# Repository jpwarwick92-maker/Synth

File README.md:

# Synth

Firmware for a DIY 8-voice subtractive poly synth, and a browser prototype that runs
that same firmware with an on-screen control panel, so the sound engine, the display
and the panel layout can be played before any hardware exists.

## What is here

| Path | What it is |
|---|---|
| `firmware/` | The firmware core in portable C++: sound engine, oscillator engines, arpeggiator, vocoder, effects, MIDI handling, the parameter table, control logic, patches and panel take-over, soft-control modes and display drawing. No heap, no standard library, nothing platform-specific. |
| `targets/web/` | Thin wrapper that builds the core as a WebAssembly module for the browser. |
| `targets/teensy/` | Thin wrapper that builds the core for the Teensy 4.1 (PlatformIO). Compile-checked on every push; not yet run on a board. |
| `web/` | The page. It is fake hardware only: it draws the panel, reports raw control positions and MIDI bytes, shows the firmware's display buffer, lights each control's label in the colour the firmware asks for, and plays its audio. It can also plug a microphone into the firmware's audio input, send it MIDI clock, and pass on what leaves by its MIDI out. |
| `layouts/a3.json` | The panel layout in millimetres. The page draws whatever this file says. |
| `tests/native/` | Engine and display tests that render audio and display frames with no browser. `make test` leaves the frames, and a few of the renders as sound files, in `build/out`. |
| `tests/page/` | Page tests in a headless browser (mouse, touch, MIDI). |
| `docs/controls.md` | Every control with its MIDI controller number, generated from the firmware's table. |
| `hardware/` | KiCad 10 projects for the circuit boards (clock hub main board, one-LED tile) and the shared `Synth` parts library. See `hardware/README.md`. |

## The rule that keeps the code portable

Everything the real synth will run lives in `firmware/` and is built three ways from
the same files: natively for the tests, as WebAssembly for the page, and for the Teensy.
The page never decides what a control does. It reports "pot 10 is at 2731" or "button 36
went down", exactly as panel hardware would, and shows the pixels the firmware draws. An
on-screen knob never moves by itself, because a real one cannot.

Rules for code in `firmware/`:

- no memory allocation, at start-up or while playing;
- audio in blocks of at most 128 samples. Safe at any sample rate; made for 44.1 kHz
  (the Teensy) and 48 kHz (the page asks the browser for it). Above 48 kHz the longest
  delay is shorter than its setting says and the reverb's lines are scaled down;
- only `<stdint.h>` and `<stddef.h>`; maths comes from `fw_math.h`;
- the display is drawn with pixels, lines, fills and a bitmap font only, in a fixed
  set of colours named by what they are for (the frame is 4 bits per pixel), and no
  text smaller than 2 mm tall on the real display (font scale 2);
- large tables and delay lines are 16-bit where that is inaudible, to fit the
  Teensy's 1 MB of RAM. They stay in RAM: reading them from flash in the audio loop
  is too slow.

## Build and run

Needs `make`, `g++`, `clang++` with the WebAssembly linker (`lld`), Node 22 and Python 3.

```sh
make test        # engine and display tests
make site        # build the page into build/site
make serve       # serve it on http://localhost:8080
make sanitize    # the same tests with the compiler's memory checker on (slower)
make page-test   # a long run of the browser build, then the page tests
                 # (needs Playwright: cd tests/page && npm install && npx playwright install chromium)
make docs        # regenerate docs/controls.md
```

Open the page in Chrome, plug in a MIDI keyboard, press Start and allow MIDI.
The page must be served from `localhost` or over HTTPS; browsers do not allow MIDI
or the audio engine on a plain file.

Teensy compile check: `pip install platformio && pio run -d targets/teensy`.

## Using the page

- Knobs, selectors and encoders: press and circle the pointer round the control and it
  turns with you. The **Knobs** button switches to dragging up and down instead.
- Scrolling over any control also moves it (two fingers on a trackpad, or a mouse wheel).
- Hold Shift for fine movement.
- Selectors: you can also tap a stop's label. Encoders: double-tap to push.
- Faders follow the pointer along their slot.
- **Zoom display** shows the display enlarged with every pixel visible. On the panel it
  is drawn at its true physical size, which on most screens is fewer pixels than the real
  320x240 display has.
- **1:1 size** shows the panel at true physical size. It asks once for calibration
  against a bank card held to the screen.
- Each control's label stands in for a back-lit label on the real panel. It is plain
  warm white normally, and glows red to amber or blue when the control is off a loaded
  patch (see Patches below).
- **Rough pots** (among the test aids) feeds the firmware pot readings as real hardware
  gives them: a few counts of jitter and a trace of the neighbouring pot. The firmware
  smooths them, so nothing should look or sound different with it on.
- Below the panel are test aids that are not part of the synth: stand-in pitch-bend
  and mod wheels, a Test note button that holds a chord, a sustain-pedal switch and Panic.
  They behave as a keyboard set to the channel the synth plays, and Panic is sent on
  every channel.
- **Mic in** plugs this computer's microphone into the synth's audio input (use
  headphones, or the speakers feed back). The dot beside it is the light by the input
  jack. **Test clock** sends MIDI clock into the synth's MIDI in at the tempo in the box
  beside it, as a DAW or a clock hub would; pressing it again sends stop.
- **MIDI out** in the top bar picks the device the synth's MIDI out jack is plugged
  into. A MIDI keyboard, or a DAW sending notes and clock, arrives at the synth's MIDI in.

## What the prototype covers

The whole panel (layout A3) driving the voice: two oscillators plus sub and noise,
mixer, multimode filter (12 or 24 dB) with drive, filter and amp envelopes, one LFO,
glide, and poly, mono and unison modes. The display shows a home screen with a live
scope and a visual for each control as it moves.

**Panel features added while prototyping.**

- **Drift** makes each voice slightly and slowly out of tune with the others, in pitch
  and filter cutoff, as the voices of an analog poly are. At zero every voice is exact.
- **Spread** fans the voices out between the two speakers.
- **Supersaw** is the fifth stop on each Wave selector: seven saws, with Macro setting
  how far apart they are tuned.
- **DRAW** is the sixth stop on each Wave selector: a wave you draw yourself (see
  "The drawn wave" below). The Wave selectors and LFO Shape show a small picture of each
  wave instead of its name, with a doodle line for DRAW and a stepped line for random.
- **Sync** restarts oscillator 2 with every cycle of oscillator 1. With Sync on, the
  Mod page's Env>Pitch moves oscillator 2 only, which gives the classic sync sweep.
- **X-Mod** lets oscillator 2 bend oscillator 1's phase, even with oscillator 2's
  fader down.
- **Arp** has its own section: Mode, Octaves, Tempo, Gate, Hold and Chord.
- **LFO Sync** is a three-stop selector in the LFO section. FREE: one LFO that takes no
  notice of the keys. KEY: it starts again when a note begins from silence. VOICE:
  every voice has its own LFO, each a little out of step and a little off the others'
  pace, so a held chord shimmers instead of moving as one.
- **Chorus** is a knob in the Voice section, with a Type switch beside it. CHORUS is two
  slowly swept copies, one per side. ENSEMBLE is three, a third of a cycle apart, swept
  by a slow and a fast wave at once: a swirl with no one wobble to be heard in it.
- **Sub pitch** is a selector beside the Sub fader: two octaves below oscillator 1, one
  below, a fifth above, or an octave above. Sub detune (up to 25 cents either way) is
  on the Engine page.
- **Chord** remembers the shape of a chord. Hold a chord and press Chord; after that
  each single key plays that chord, moved to the key. With the arp running, one key
  arpeggiates it. Press Chord again to forget it.
- **Ladder filter** is a third setting of the filter slope on the Engine page
  (12 dB, 24 dB, Ladder): four stages with feedback round all of them, low-pass only,
  losing some bass as resonance rises. The Type selector does nothing while it is chosen.

The layout keeps knob, selector and encoder centres at least 22 mm apart and fader
centres at least 17 mm apart, and the page tests fail if any label overlaps another
label, a control, or its section's outline. The sections sit on a grid: two rows of
equal height on five shared columns, with the same gap between every pair of
neighbours. The panel is 530 x 152 mm.

**The display.** Every control has a picture that follows it: turn a control and its
picture changes, or says in words why there is nothing to show (a delay with its mix
at zero, an oscillator playing a flat drawing). The tests enforce this for every panel control and
every value on the encoder pages, from the default settings, with further tests for
the settings under which a control does nothing. On an encoder page the picture takes
the place of the scope for a moment after an encoder is turned.

The display has two sets of colours, chosen on the Setup page. **Amber** is ambers and
orange on black, for a bare display. **White** is warm whites told apart by brightness,
for a display behind amber acrylic, which turns white into amber by itself. The page's
**Amber acrylic** button lays that sheet over the on-screen display so the white set can
be judged as it will look.

**Oscillator engines.** Each oscillator has an Engine button that steps through four
engines. The Wave selector and the timbre controls mean something different under each:

| Engine | Wave selector | Macro | Color |
|---|---|---|---|
| VA | saw, square, triangle, sine, supersaw, DRAW | shapes the wave (below) | none |
| FM | ratio 1:1, 2:1, 3:1, 3.5:1, 4:1, 0.5:1 | FM amount | feedback |
| Wavetable | table 1 to 5, and table 6: the drawing | position in the table | none |
| Pluck | exciter: noise, soft, snap, string, pick, the drawing | damping | decay |

Oscillator 1's Macro is the panel knob. Its Color, and oscillator 2's Macro and Color,
are on page 2 of the Engine mode.

**Macro shapes the wave** under the VA engine, whichever wave is selected. At zero each
wave is exactly what it was before Macro shaped it (tested bit for bit), and costs no more.

| Wave | Macro (display name) | What it does |
|---|---|---|
| Saw | SOFTEN | Rounds the corners, like the slower reset of an analogue oscillator: a filter that follows the note, from 256 times its pitch down to 1.5 times. |
| Square | PULSE WIDTH | As before. |
| Triangle | SHARK FIN | Bends the ramps into capacitor curves, from a triangle to a full shark fin (a filter that follows the note, from 0 to 1 times its pitch). |
| Sine | SQUARE UP | Adds a square's odd harmonics (3rd to 15th), more of them as Macro rises: a pure sine at zero, close to a square at full. |
| Supersaw | SPREAD | How far apart the seven saws are tuned, as before. |
| DRAW | SOFTEN | Rounds the drawing's corners, as on the saw. |

Each shape is held to the loudness of its Macro-zero wave as Macro turns, and each
keeps high notes clean (nothing louder than -60 dB between the harmonics). On a
patch, Macro now matters wherever it rests on a saw, triangle or sine.

**The drawn wave.** Each patch has a drawing: 16 points joined by straight lines, one
cycle of a wave, shared by both oscillators. A new patch starts with a saw. It is
drawn on the third Engine page:

| Encoder | Turn | Push |
|---|---|---|
| 1 | moves along the 16 points | paint mode on or off: moving along then copies the height onto each point passed |
| 2 | raises or lowers the point | puts the point on the centre line |
| 3 | chooses a starting shape: saw, square, triangle, sine, flat | replaces the drawing with it |
| 4 | | smooths the drawing a little |

The page shows the drawing with the point being edited picked out, and says so when
neither oscillator is playing it. Notes that are sounding follow the drawing as it
changes, a moment behind, with a 20 ms crossfade so nothing clicks. The drawing is
turned into band-limited tables (one per octave) so it stays clean on high notes;
that takes longer than an audio block, so it is done in spare time between other work
(`fw::work()`, called by the Teensy's main loop and by the page between audio blocks).
A drawing is played at about a saw's loudness, whatever its shape; a flat one is
silent. Under the pluck engine the string is struck with the drawing's shape, at the
other exciters' loudness. The drawing is never an FM modulator (its partials would
spread far above the note and fold back), so under FM the sixth stop is a 0.5:1 ratio.

**Soft-control modes.** A mode button puts four values on the encoders. Pressing the
lit button steps to the mode's next page if it has one, then returns home. Pushing an
encoder restores its default.

| Button | Page | Encoders |
|---|---|---|
| FX 1 | Delay | time, tone, feedback, mix |
| FX 2 | 1: Compressor + reverb | compressor, reverb size, reverb tone, reverb mix |
| FX 2 | 2: Vocoder | amount, formant, consonants, smooth |
| Mod | Mod | LFO fade-in, velocity to cutoff, filter envelope to pitch, duck |
| Engine | 1: Voice | unison detune, sub detune, bend range, filter slope (12 dB, 24 dB, ladder) |
| Engine | 2: Osc engines | osc 1 Color, (empty), osc 2 Macro, osc 2 Color |
| Engine | 3: Draw | the patch's drawing (see "The drawn wave") |
| Patch | 1: Patch | slot (push to load), save here (push), guide lights, manual (push) |
| Patch | 2: Name | cursor, (empty), letter, (empty) |
| Patch | 3: Setup | display colours (amber, or white for behind amber acrylic); label lights (steady or dance) |
| Patch | 4: MIDI | clock (internal, MIDI jack, USB), channel (all, 1 to 16), thru, clock out |
| Patch | 5: Input | source (line, mic), gain (0 to 60 dB), send to (off, mix, effects), (empty) |

**Settings.** The MIDI and Input pages hold settings about the instrument, not the
sound: they are kept over a restart and a patch never changes them.

**Clock.** With Clock on INT the arp and the duck run at the Tempo knob's setting. On
MIDI or USB they follow the MIDI clock arriving at that input, and the Tempo knob is not
used (its picture says so, and shows the clock's tempo).

- The arp's sixteenth notes fall on the clock's grid. The tempo is the average spacing
  of the last beat's ticks, and the arp steps on a position that runs on smoothly at that
  tempo and is nudged towards each tick, so ticks that arrive a few milliseconds early
  or late (as they do from a computer) still give even steps.
- **Start** begins the pattern again on the next tick, and nothing plays until that
  tick. **Stop** holds the arp silent until start or continue; notes latched by Hold
  stay latched. **Continue** carries on from where it stopped, in the beat and in the
  pattern. A **song position** message moves the beat to the sender's playhead.
- After a stop, if the clock itself has gone as well (a DAW usually stops sending it), a
  fresh chord is not kept waiting: it plays from the Tempo knob. What was latched before
  the stop stays silent.
- A key pressed up to a quarter of a step late still gets that step; later than that it
  waits for the next one.
- If no clock is arriving (none yet, or it has stopped coming for half a second) the
  Tempo knob is used meanwhile, so the synth is never silent for want of a cable.
- Clock at the input that is not selected is ignored.

**MIDI in and out.** There are two connections, the MIDI jacks and USB. Notes and
controllers are played from either, on the Channel set (or on every channel).
Changing Channel lets go of every note and the pedal, since their note-offs may now
arrive on a channel that is no longer listened to.
With **Thru** on, every note and controller message that arrives is passed on, whatever
its channel: both inputs to the MIDI out jack, and the MIDI jack's input to USB (never
USB back to USB). With **Clock Out** on, the clock the synth is running on is sent too:
its own, 24 ticks to a beat at the Tempo knob's setting, when it keeps time itself; the
incoming clock with its start, stop and continue when it is following. System-exclusive
messages are not passed on. If Thru is switched off while notes are held, or a message
could not be passed on because nothing was reading the output, "all notes off" is sent
on every channel, so nothing further down the chain is left sounding. The synth's own
clock is made in the audio blocks, so on the Teensy each tick can leave up to 2.9 ms
late; the tempo it carries is exact. On the page, a device that is both a MIDI input
and the one picked for MIDI out is not listened to while it is the output: the synth
would be handed its own messages back, round and round. Use one bus each way.

**Audio input.** The firmware takes a stereo input beside its output. **Send To**
chooses where it goes: nowhere, straight to the output beside the synth's own sound
(Mix), or into the effects with it (FX). The Volume knob turns it up and down with the
synth: at the knob's usual setting the input passes at its own level. A line input is
stereo; a microphone is one channel and comes out on both sides. **Gain** is what the firmware asks of the preamp in
front of the converter, so on real hardware it is analog gain. The Input page shows the
level against the converter's limit, and the light by the jack is dark with no signal,
amber with one, and red for nearly half a second whenever the input reaches the limit.
With Send To off the output is exactly what it would be with nothing connected. The
vocoder listens to this input whatever Send To is set to.

**Vocoder** (FX 2, second page). The synth's sound, shaped by a voice at the audio
input: play notes, speak into the microphone, and the notes take on the words. The voice
is split into 16 bands from 140 Hz to 7 kHz and the level of each is followed; the
synth's sound is split into the same bands and each is turned up and down by the voice's.
It sits between the voices and the effects, on one channel (the chorus and reverb after
it can widen it again), and its four values are stored in patches.

- **Vocoder** is the amount: how much of the synth's own sound is replaced by the
  vocoded sound. At 0 it is out of the path altogether. At 100% nothing is heard unless
  a voice is arriving.
- **Formant** moves the voice's shape up or down the synth's sound, up to an octave
  either way: up sounds smaller and brighter, down larger and darker.
- **Consonants** adds hiss to the synth's top three bands, so S, T, F and SH are heard
  even on a dull sound. It is added only for breath sounds (a voice whose strength is
  nearly all at the top), and only while a note is held.
- **Smooth** sets how fast each band's level falls when the voice does, from 8 ms
  (crisp, every syllable distinct) to about a third of a second (slurred).
- With the vocoder on, its page shows the sixteen bands moving with the voice, and says
  why if nothing can be heard: no signal at the input, or no note held.
- It works best on a bright, steady sound: saw or supersaw, filter well open, sustain up.
  Set the input's Gain so the light by the jack is amber, never red. Leave Send To off
  unless the plain voice should be heard as well.

**Patches.** Sixteen slots. Every main control is a real pot, fader or switch, so
loading a patch cannot move it. Instead:

- **Saving** stores every value except master volume and Hold, and the drawing.
  Patches saved by builds before the drawing (patch version 1 or 2) are not loaded:
  their slots read as empty. An empty slot saves on
  one push of encoder 2; a used slot asks for a second push within three seconds.
- **Loading** (push encoder 1, or send a MIDI program change) sets the sound from the
  stored values. Any control that is somewhere else is then *following*: the sound uses
  the stored value, and the control is ignored until it takes over.
- **Take-over.** A pot or fader takes over when it is moved through the stored value, or
  lands within 2.5% of its travel of it (1% for Detune), so the sound never jumps.
  Touching one that has not got there shows a picture of where the panel and the patch
  are and which way to go. A selector or switch takes over on any change.
- **Guide lights.** After a load, the label of each control that is off the patch
  glows, steadily. A control that has to come up is deep red when it is a long way
  below the patch and warms to amber as it closes in; one that has to come down is deep
  cold blue far off and pales as it nears. At the patch's value the label goes back to
  plain warm white, so when no label is coloured the panel matches the patch. A
  selector's light stays on until it is on the patch's stop, even though it is already
  live. Encoder 3 switches the lights between On, Tint (a dim amber on anything still
  following) and Off.
- **Manual** (push encoder 4) drops the patch: every control goes live where it stands.
- The home screen shows the slot and name, with `*` once the sound has changed.
- A MIDI controller message for a panel parameter is treated like a one-control load:
  the control follows the incoming value until it is moved through it (or, for a
  selector, changed). That goes for master volume too.

**Dance** (Setup page, encoder 3) makes the label lights move with the sound instead of
staying plain. Each section's labels follow what that section is doing: the LFO's rise
and fall with it; the envelope faders light in turn as a note passes through Attack,
Decay, Sustain and Release; Cutoff follows the filter envelope's sweep; a ripple runs
from the oscillators through the mixer to the filter on every note; the arp's flash on
each step; Volume follows the level. Everything stays between a dim amber and a bright
cream. While a loaded patch has controls to bring back, the dance stops and the guide
lights show. On hardware this mode changes the LEDs' current many times a second, so
their supply has to be kept well away from the audio's.

On the Teensy the slots sit in the on-board EEPROM for now, which is why there are
sixteen; a memory card or the board's flash would hold far more.

**Arpeggiator and Hold.** The arp plays the held notes as sixteenth notes: up, down,
up-down, random or as played, over 1 to 4 octaves, at 40 to 240 BPM. **Hold** keeps
notes sounding after the keys are let go; the next chord replaces them. It works with
the arp on or off. While the arp runs, the sustain pedal acts as a temporary Hold.
Neither Hold nor Chord comes back on by itself after a restart.

**The LFO's MACRO destination** (it was PW) moves whatever Macro does on that oscillator:
pulse width on a square, the saw's softness, the shark fin, the sine's squaring, the
supersaw's spread, the drawing's softness, FM amount, wavetable position, pluck damping.
With Macro at zero only the upper half of the sweep acts.

**When the processor is short of time.** A target that can time its audio (the Teensy)
reports how much of each block's time was used. If that stays above about 85% the
engine drops voices one at a time, down to two at the fewest, and gives them back
after a calm spell, instead of falling behind. Saving the state (the control
positions and settings, a second after the last change) waits for silence, for up to
half a minute, because on real hardware a save can interrupt the sound. The page's
storage costs the sound nothing, so there it does not wait. Saving a patch is written
at once on either: it is asked for by hand, and must not be lost.

**Compressor** (FX 2 page) turns the loud parts down and everything back up, so one
note and a full chord come out nearer the same level and soft notes and tails are
lifted. Its one control lowers the threshold, raises the ratio (to 4:1) and adds
make-up gain together. At zero it is out of the path altogether.

**Duck** (Mod page) dips the level just after every beat and lets it come back before
the next, as a compressor keyed from a kick drum does. The beat is the arp's Tempo, or
the MIDI clock's when one is being followed (the dips then fall on that clock's beats).
On the synth's own clock, while the arp runs the beat is counted from its steps, four to
a beat, so the two cannot slip apart; otherwise (the arp off, or no key held) it runs on
by itself, starting again with any note played from silence. The first
hundredth of a second of each beat is let through, so a note played on the beat keeps
its attack.

The order is vocoder, chorus, delay, reverb, compressor, duck, then the output
limiter.

**Output** is stereo once Spread, the chorus or the reverb is in use. With Spread at
zero and every effect off, both channels carry exactly the same signal.

Not built yet: sending the input through the voices' filter, loading patches
from files, and the iPad version (Safari on iPad has no Web MIDI, so it needs a small
wrapper app).

## Publishing

`.github/workflows/build.yml` runs the tests and the Teensy compile on every push, and
publishes `build/site` to GitHub Pages on pushes to `main`. Pages must be switched on
once in the repository settings, with **GitHub Actions** as the source.

Third-party material is listed in `THIRD_PARTY.md`.

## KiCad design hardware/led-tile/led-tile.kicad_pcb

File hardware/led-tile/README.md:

# LED tile, rev A

One reverse-mount SK6812 MINI-E on a 12 × 10 mm board, used to backlight one panel
label. The clock hub uses 12 of them and the synth about 43. Tiles are chained by three
hand-soldered wires each (+5 V, data, GND), from each tile's OUT pads to the next
tile's IN pads.

| Front (faces the panel) | Back (parts and wire pads) |
|---|---|
|  |  |

Schematic: [images/schematic.svg](images/schematic.svg)

## What's on it

| Ref | Part | Why |
|---|---|---|
| D1 | SK6812MINI-E (OPSCO), KiCad footprint `LED_SK6812MINI-E_3.2x2.8mm_P1.5mm_ReverseMount` | The light. Reverse-mount: it sits on the back and shines through a hole in the board. |
| C1 | 100 nF, 0603, X7R, 16 V or more | Local supply for D1's driver chip. The datasheet calls the capacitor "essential". |
| R1 | 330 Ω, 0603 | In series with DIN. The datasheet asks for series resistors on the data pins, against static and surges. That matters here because every tile is hand-wired. |
| J1 | `Synth:WirePads_1x03_P2.80mm` | IN wire pads: GND, data, +5 V. Not a part; left out of the BOM. |
| J2 | same | OUT wire pads: GND, data, +5 V. |

## Board

- **Size:** 12 × 10 mm, 2 layers, **0.8 mm thick** (see the stack-height question below).
- **Orientation key:** one corner is cut at 45°, on the IN/GND corner. A matching pocket in the locating layer means a tile can only go in one way round, so IN and OUT can't be swapped.
- **Back:** every part and every pad. Tracks are 0.25 mm for data and 0.4 mm for power.
- **Front:** a solid ground plane under solder mask, no parts and no silkscreen. It lies flat against the spacer, and nothing printed on it can show through the lit label.
- **Ground:** reaches the plane through three vias, which are covered with mask on both sides.
- **Rules:** copper stays 0.3 mm from every board edge. The one exception is D1's pads to D1's own light hole, which sit at 0.25 mm in KiCad's footprint. `led-tile.kicad_dru` holds that exception. Check it against the chosen maker's limit before ordering.

## Things worth knowing

- **Pin numbers don't match the datasheet.** KiCad's symbol numbers D1 as 1 GND, 2 DIN, 3 VDD, 4 DOUT. The OPSCO datasheet (rev 02) calls the same pins 1 VDD, 2 DOUT, 3 GND, 4 DIN. KiCad's symbol and footprint agree with each other and with the real part: the footprint was checked pad by pad against the datasheet drawing, seen from the back. Go by the pin names. If the board maker's placement preview shows D1 turned, check it by the package's cut corner, which is the GND corner, not by "pin 1".
- **Seen from the back, IN is on the right.** The back silkscreen is printed to read correctly from the back.
- **Data level.** DIN needs at least 0.7 × VDD, which is 3.5 V at 5 V. The first tile must be fed from the main board's 5 V buffer, never straight from the Teensy's 3.3 V pin. Each tile's DOUT then drives the next tile at 5 V.
- **Current.** Each LED draws up to 12 mA per colour, 36 mA at full white, so 12 tiles can draw 0.43 A. Brightness is capped in firmware.
- **Moisture.** The LED is moisture-sensitive (MSL 5a: 24 hours out of its bag), and its peak reflow temperature is 240 °C. That matters only if the LEDs are ever hand-soldered from a bag kept at home.

## Open question: stack height

The tile is about 1.9–2.0 mm deep, from its front face to the back of the LED. The back
of D1 sticks out about 1 mm behind the 0.8 mm board, and C1 about 0.8 mm. The hub
spec's locating layer is about 1.6 mm, so the tile doesn't fit as specced. Options:

1. **A 2.0 mm or thicker locating layer.** The panel stack grows by 0.4 mm or more, so the 17 mm shaft rule grows too.
2. **Clearance holes in the steel sub-panel** under each tile's LED and C1. The steel is laser-cut anyway, so the holes cost nothing, and the stack height stays the same. The PET insulator still covers them.
3. **A thinner board** (0.6 mm). This saves only 0.2 mm, and the datasheet warns about bending stress on boards under 0.5 mm.

To settle at the feel-and-fit mock-up (hub test H2).

## Still to do before ordering

- [ ] Settle the stack-height question above.
- [ ] Panelise: a sheet of 12 tiles with snap-apart tabs and the maker's rails and fiducials (a KiCad plugin such as KiKit does this). Keep the LED's pads at right angles to the snap lines, so snapping doesn't bend the joints.
- [ ] Pick the maker. Confirm that it assembles the LED on the back, in its reversed position, and accepts the 0.25 mm pad-to-hole gap. Choose white solder mask if offered, so light reflects up into the pocket.
- [ ] Choose exact R1 and C1 part numbers from the maker's stock.
- [ ] Print the board 1:1 on paper and lay a real LED on the footprint (hub test H4).
- [ ] Independent review of the schematic and board (hub test R4).

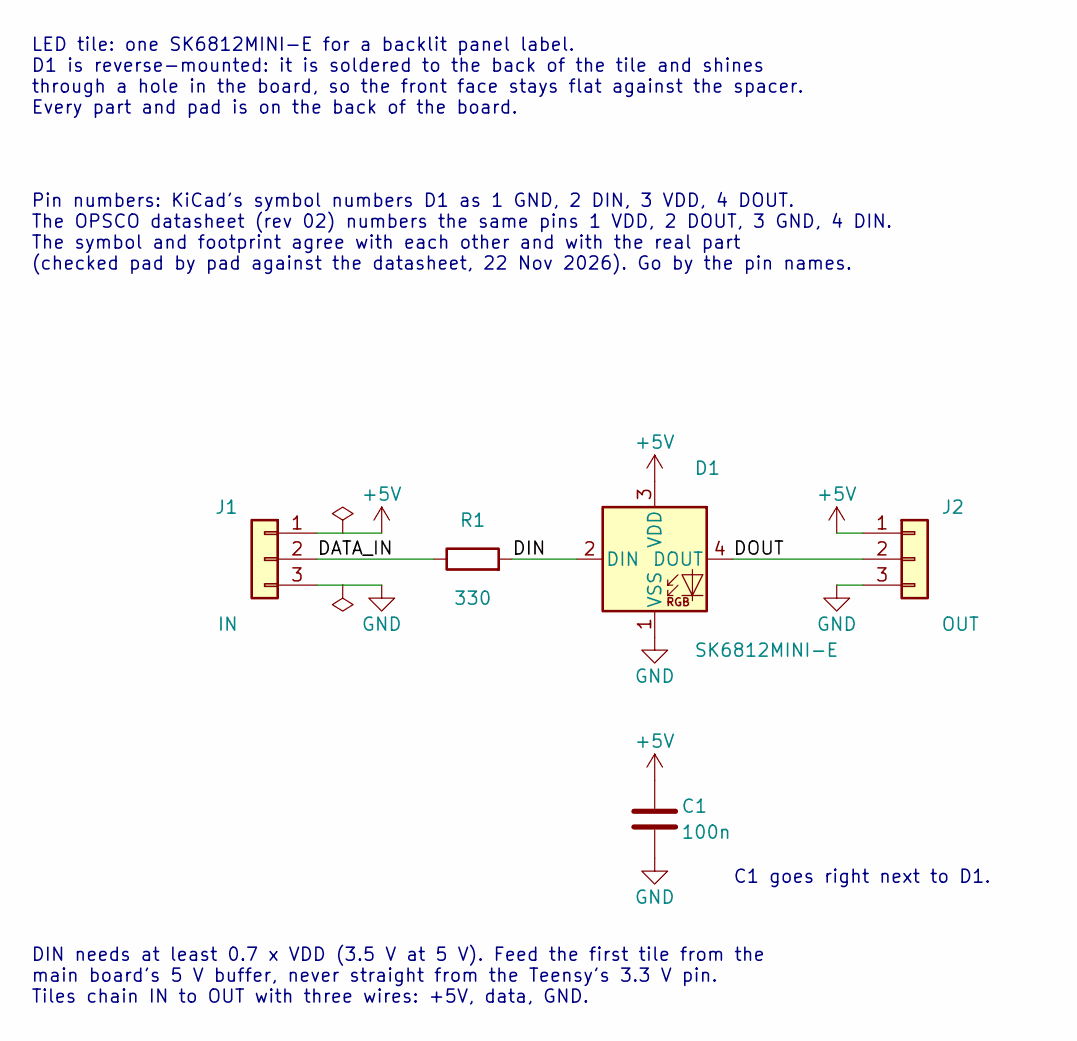
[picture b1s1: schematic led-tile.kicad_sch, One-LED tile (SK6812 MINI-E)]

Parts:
C1: 100n; C_0603_1608Metric_Pad1.08x0.95mm_HandSolder
D1: SK6812MINI-E; LED_SK6812MINI-E_3.2x2.8mm_P1.5mm_ReverseMount
J1: IN; WirePads_1x03_P2.80mm
J2: OUT; WirePads_1x03_P2.80mm
R1: 330; R_0603_1608Metric_Pad0.98x0.95mm_HandSolder

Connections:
+5V: C1.1, D1.3 (VDD), J1.1, J2.1
/DATA_IN: J1.2, R1.1
/DIN: D1.2 (DIN), R1.2
/DOUT: D1.4 (DOUT), J2.2
GND: C1.2, D1.1 (VSS), J1.3, J2.3

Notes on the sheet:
C1 goes right next to D1.
LED tile: one SK6812MINI-E for a backlit panel label. D1 is reverse-mounted: it is soldered to the back of the tile and shines through a hole in the board, so the front face stays flat against the spacer. Every part and pad is on the back of the board.
DIN needs at least 0.7 x VDD (3.5 V at 5 V). Feed the first tile from the main board's 5 V buffer, never straight from the Teensy's 3.3 V pin. Tiles chain IN to OUT with three wires: +5V, data, GND.
Pin numbers: KiCad's symbol numbers D1 as 1 GND, 2 DIN, 3 VDD, 4 DOUT. The OPSCO datasheet (rev 02) numbers the same pins 1 VDD, 2 DOUT, 3 GND, 4 DIN. The symbol and footprint agree with each other and with the real part (checked pad by pad against the datasheet, 22 Nov 2026). Go by the pin names.

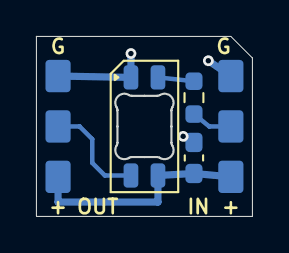
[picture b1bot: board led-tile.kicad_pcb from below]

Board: 2 copper layers, 12.0 x 10.0 mm, 5 parts (5 on the bottom side), 5 nets.
